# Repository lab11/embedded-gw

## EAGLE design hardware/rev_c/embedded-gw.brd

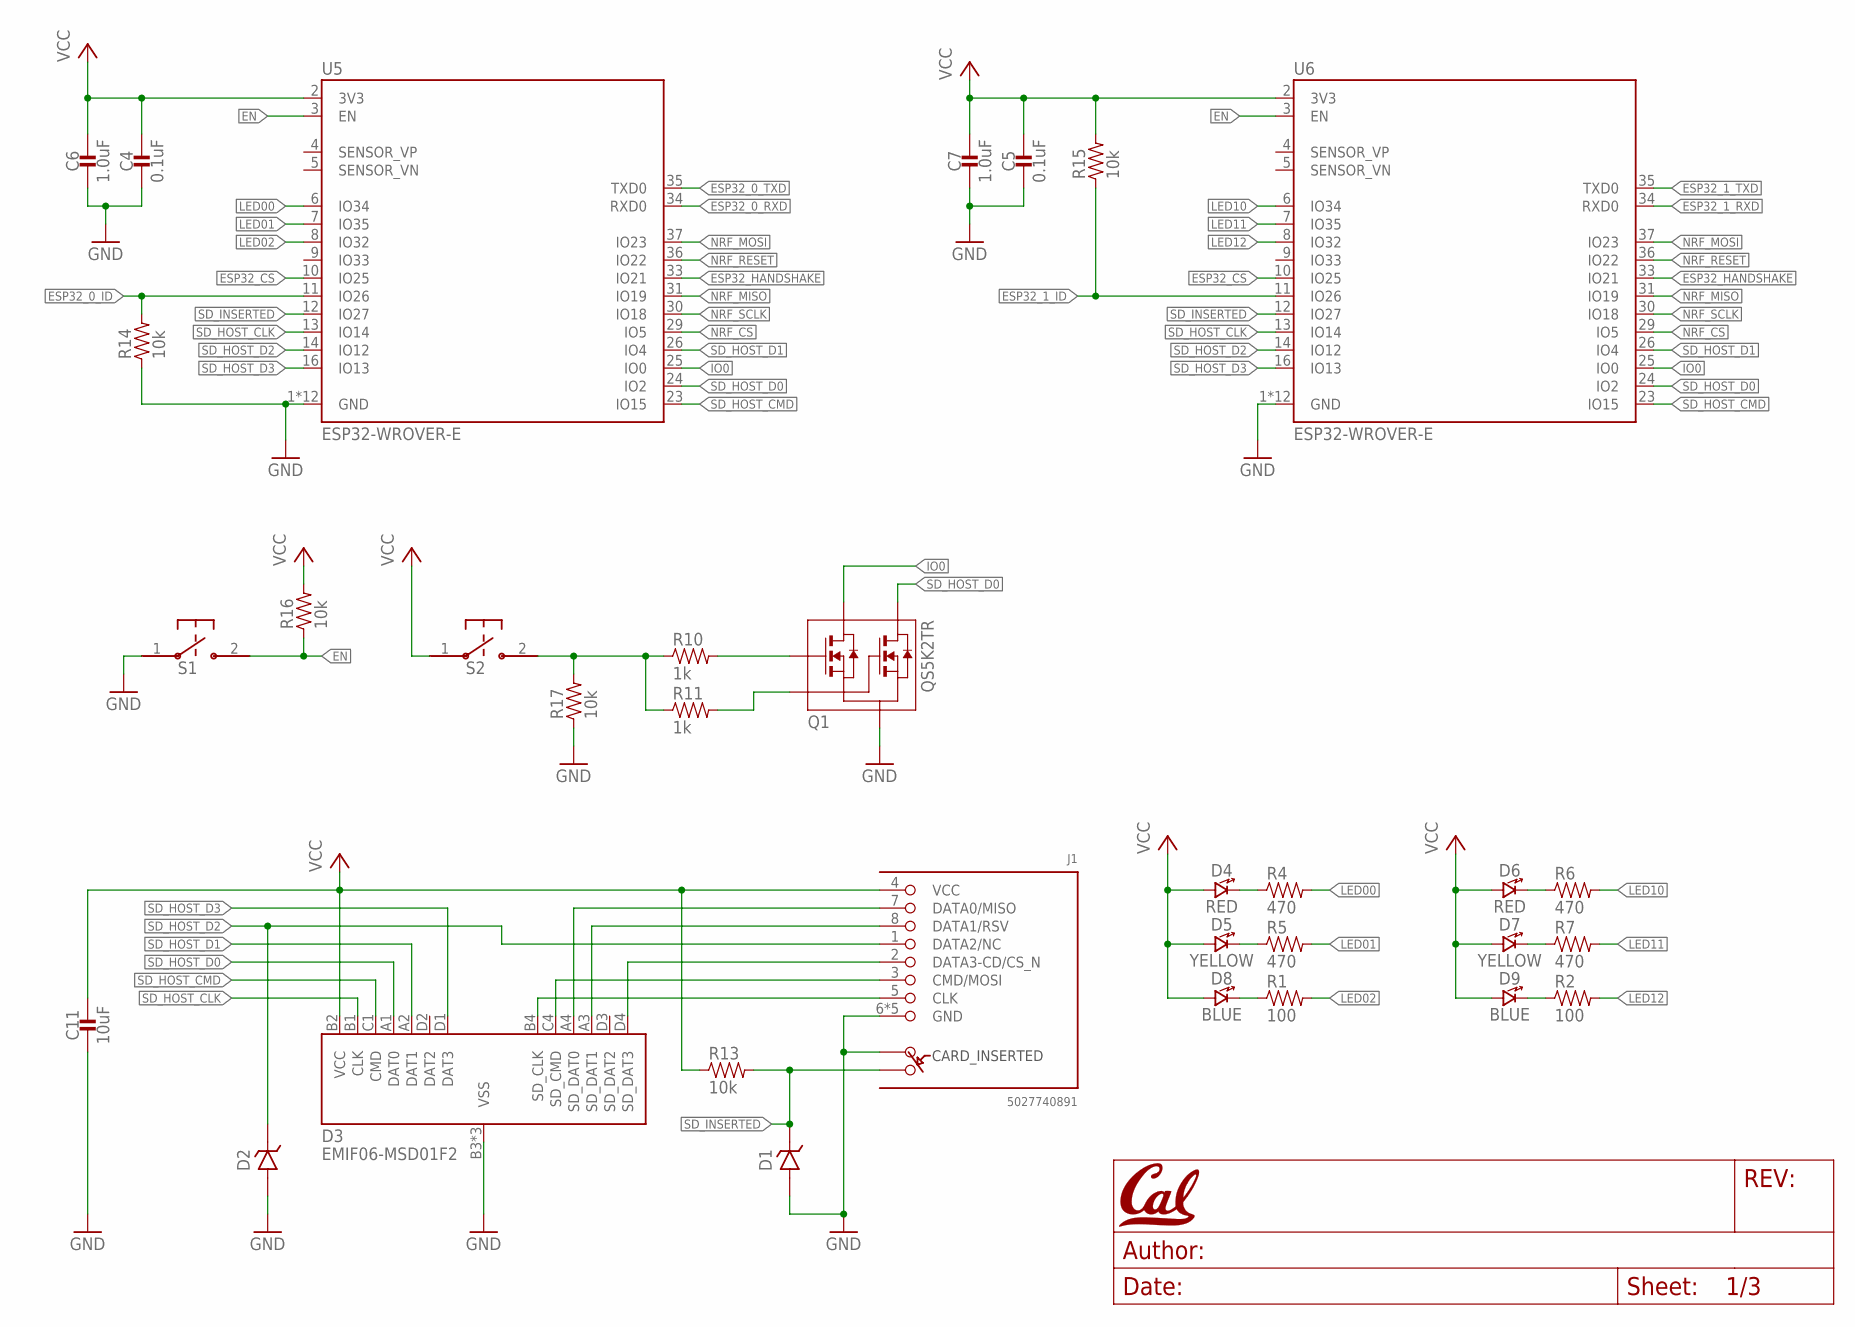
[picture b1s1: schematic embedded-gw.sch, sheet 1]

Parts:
C4, C5: 0.1uF; 0402_CAP; MPN CL05B104KQ5NNNC; DIGIKEY 1276-1511-1-ND
C6, C7: 1.0uF; 0402_CAP; MPN CL05A105KQ5NNNC; DIGIKEY 1276-1010-1-ND
C11: 10uF; 0805_CAP; MPN CL21A106KQCLNNC; DIGIKEY 1276-2404-1-ND
D1, D2: DIODE_ZENER0201; 0201_DIODE; MPN ESD7381MUT5G; DIGIKEY ESD7381MUT5GOSCT-ND
D3: EMIF06-MSD01F2; BGA16C50P4X4_192X192X65N
D4, D6: RED; LED-0603; MPN LTST-C193KRKT-5A; DIGIKEY 160-1830-1-ND
D5, D7: YELLOW; LED-0603; MPN LTST-C193KSKT-5A; DIGIKEY 160-1831-1-ND
D8, D9: BLUE; LED-0603; MPN LTST-C193TBKT-5A; DIGIKEY 160-1827-1-ND
J1: 5027740891
Q1: QS5K2TR; SOT95P280X100-5N
R1, R2: 100; 0402_RES; MPN RC0402JR-07100RL; DIGIKEY 311-100JRCT-ND
R4, R5, R6, R7: 470; 0402_RES; MPN RC0402FR-07470RL; DIGIKEY 311-470LRCT-ND
R10, R11: 1k; 0402_RES; MPN RMCF0402JT1K00; DIGIKEY RMCF0402JT1K00CT-ND
R13, R14, R15, R16, R17: 10k; 0402_RES; MPN RMCF0402JT10K0; DIGIKEY RMCF0402JT10K0CT-ND
S1, S2: B3U-1000P
U5, U6: ESP32-WROVER-E

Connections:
!NRF_RESET: U5.36 (IO22), U6.36 (IO22); also elsewhere on the board
!SD_INSERTED: D1.P$1 (CATHODE), J1.SWITCH (B), R13.2, U5.12 (IO27), U6.12 (IO27)
EN: R16.1, S1.2, U5.3 (EN), U6.3 (EN)
ESP32_0_ID: R14.2, U5.11 (IO26)
ESP32_0_RXD: U5.34 (RXD0); also elsewhere on the board
ESP32_0_TXD: U5.35 (TXD0); also elsewhere on the board
ESP32_1_ID: R15.1, U6.11 (IO26)
ESP32_1_RXD: U6.34 (RXD0); also elsewhere on the board
ESP32_1_TXD: U6.35 (TXD0); also elsewhere on the board
ESP32_CS: U5.10 (IO25), U6.10 (IO25)
ESP32_HANDSHAKE: U5.33 (IO21), U6.33 (IO21)
GND: C4.2, C5.2, C6.2, C7.2, C11.P$2 (2), D1.P$2 (ANODE), D2.P$2 (ANODE), D3.B3 (VSS), D3.C2 (VSS), D3.C3 (VSS), J1.6 (GND), J1.DETECT (A), J1.GND1 (GND), J1.GND2 (GND), J1.GND3 (GND), J1.GND4 (GND), Q1.2 (S), R14.1, R17.1, S1.1, U5.1 (GND), U5.15 (GND), U5.38 (GND), U5.GND1 (GND), U5.GND2 (GND), U5.GND3 (GND), U5.GND4 (GND), U5.GND5 (GND), U5.GND6 (GND), U5.GND7 (GND), U5.GND8 (GND), U5.GND9 (GND), U6.1 (GND), U6.15 (GND), U6.38 (GND), U6.GND1 (GND), U6.GND2 (GND), U6.GND3 (GND), U6.GND4 (GND), U6.GND5 (GND), U6.GND6 (GND), U6.GND7 (GND), U6.GND8 (GND), U6.GND9 (GND); also elsewhere on the board
IO0: Q1.5 (D1), U5.25 (IO0), U6.25 (IO0)
LED00: R4.2, U5.6 (IO34)
LED01: R5.2, U5.7 (IO35)
LED02: R1.2, U5.8 (IO32)
LED10: R6.2, U6.6 (IO34)
LED11: R7.2, U6.7 (IO35)
LED12: R2.2, U6.8 (IO32)
unnamed: Q1.1 (G1), R10.2
unnamed: Q1.3 (G2), R11.2
unnamed: R10.1, R11.1, R17.2, S2.2
unnamed: D3.C4 (SD_CMD), J1.3 (CMD/MOSI)
unnamed: D3.A4 (SD_DAT0), J1.7 (DATA0/MISO)
unnamed: D3.A3 (SD_DAT1), J1.8 (DATA1/RSV)
unnamed: D3.D4 (SD_DAT3), J1.2 (DATA3-CD/CS_N)
unnamed: D4.C (CATHODE), R4.1
unnamed: D3.B4 (SD_CLK), J1.5 (CLK)
unnamed: D5.C (CATHODE), R5.1
unnamed: D8.C (CATHODE), R1.1
unnamed: D6.C (CATHODE), R6.1
unnamed: D7.C (CATHODE), R7.1
unnamed: D9.C (CATHODE), R2.1
NRF_CS: U5.29 (IO5), U6.29 (IO5); also elsewhere on the board
NRF_MISO: U5.31 (IO19), U6.31 (IO19); also elsewhere on the board
NRF_MOSI: U5.37 (IO23), U6.37 (IO23); also elsewhere on the board
NRF_SCLK: U5.30 (IO18), U6.30 (IO18); also elsewhere on the board
SD_HOST_CLK: D3.B1 (CLK), U5.13 (IO14), U6.13 (IO14)
SD_HOST_CMD: D3.C1 (CMD), U5.23 (IO15), U6.23 (IO15)
SD_HOST_D0: D3.A1 (DAT0), Q1.4 (D2), U5.24 (IO2), U6.24 (IO2)
SD_HOST_D1: D3.A2 (DAT1), U5.26 (IO4), U6.26 (IO4)
SD_HOST_D2: D2.P$1 (CATHODE), J1.1 (DATA2/NC), U5.14 (IO12), U6.14 (IO12)
SD_HOST_D3: D3.D1 (DAT3), U5.16 (IO13), U6.16 (IO13)
VCC: C4.1, C5.1, C6.1, C7.1, C11.P$1 (1), D3.B2 (VCC), D4.A (ANODE), D5.A (ANODE), D6.A (ANODE), D7.A (ANODE), D8.A (ANODE), D9.A (ANODE), J1.4 (VCC), R13.1, R15.2, R16.2, S2.1, U5.2 (3V3), U6.2 (3V3); also elsewhere on the board

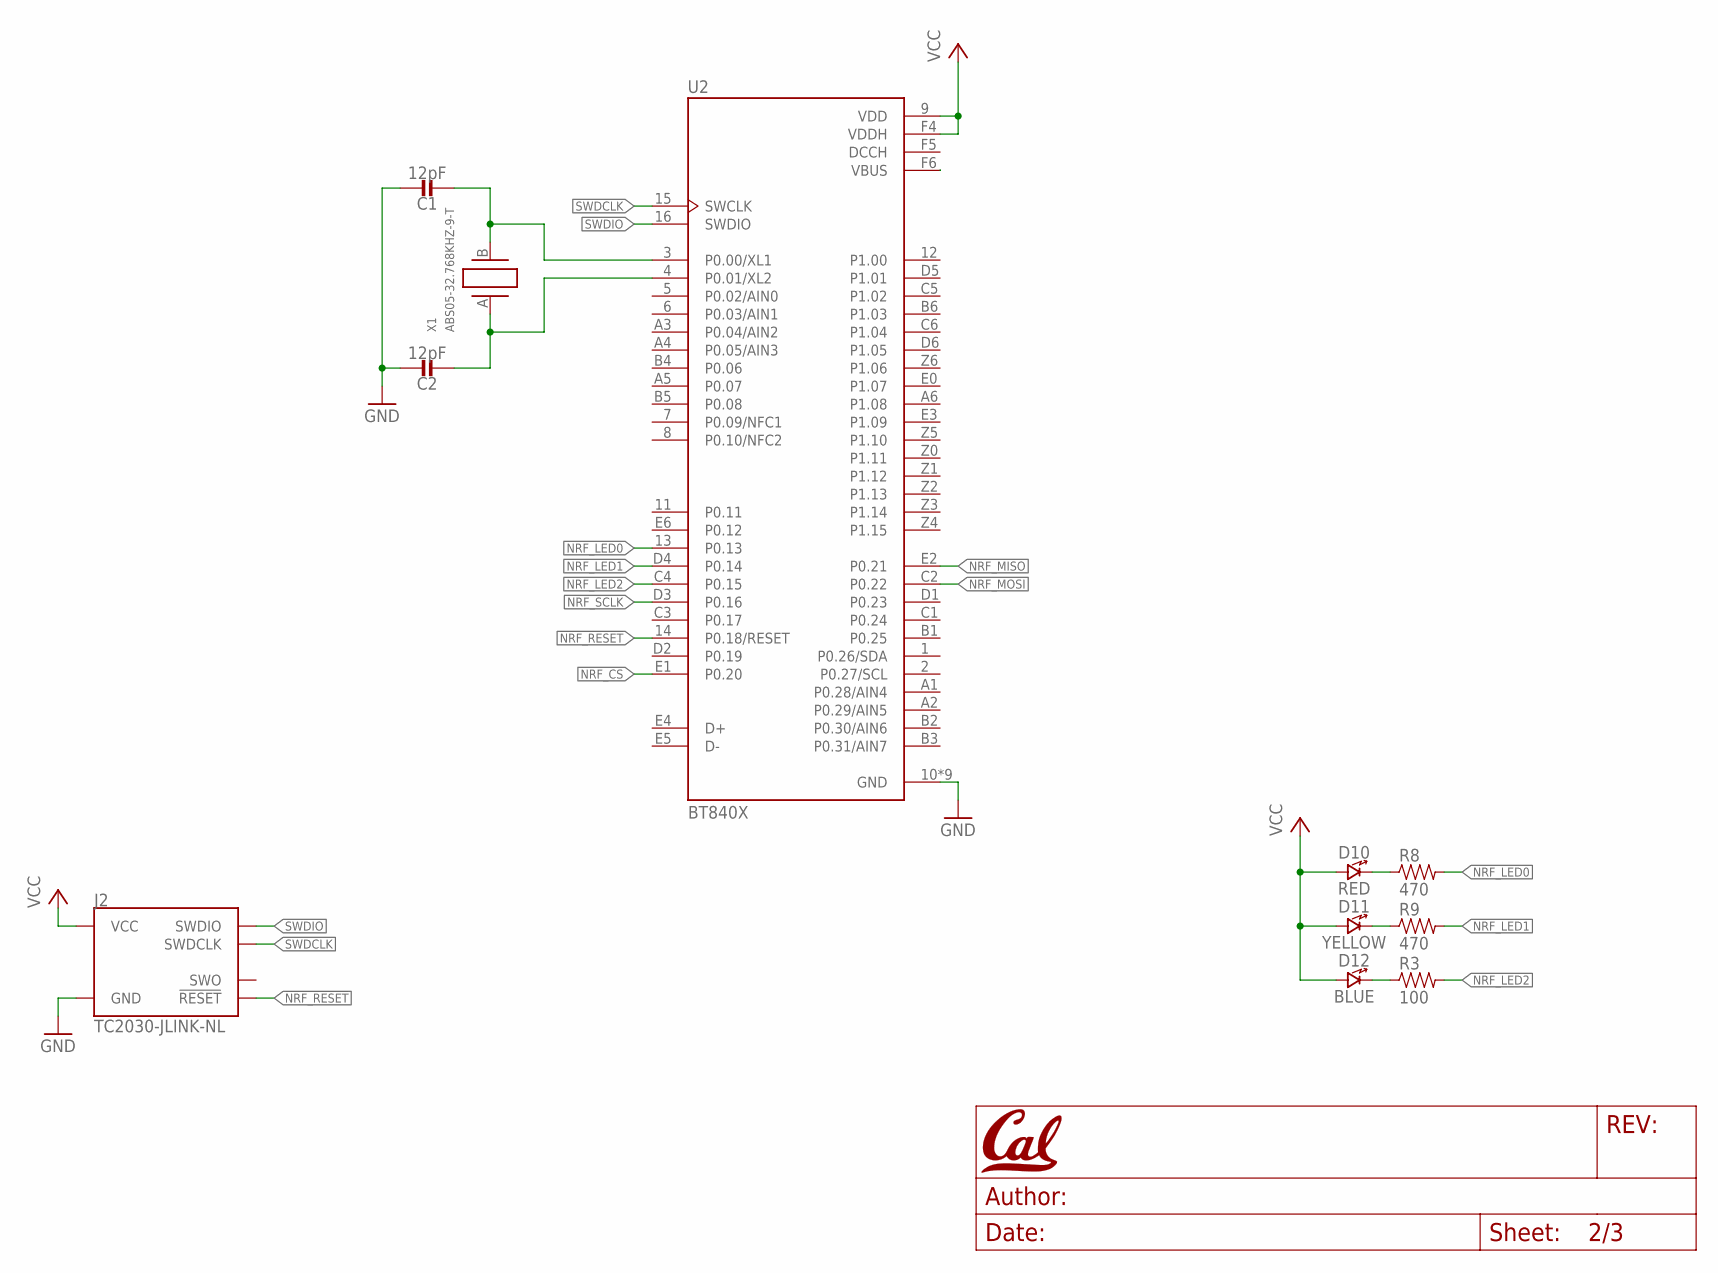
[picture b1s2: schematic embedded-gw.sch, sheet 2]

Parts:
C1, C2: 12pF; 0402_CAP; MPN GCM1555C1H120GA16D; DIGIKEY 490-GCM1555C1H120GA16DCT-ND
D10: RED; LED-0603; MPN LTST-C193KRKT-5A; DIGIKEY 160-1830-1-ND
D11: YELLOW; LED-0603; MPN LTST-C193KSKT-5A; DIGIKEY 160-1831-1-ND
D12: BLUE; LED-0603; MPN LTST-C193TBKT-5A; DIGIKEY 160-1827-1-ND
J2: TC2030-JLINK-NL; TC2030-IDC-NL
R3: 100; 0402_RES; MPN RC0402JR-07100RL; DIGIKEY 311-100JRCT-ND
R8, R9: 470; 0402_RES; MPN RC0402FR-07470RL; DIGIKEY 311-470LRCT-ND
U2: BT840X; XCVR_BT840X
X1: ABS05-32.768KHZ-9-T; ABS05

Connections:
!NRF_RESET: J2.3 (!RESET), U2.14 (P0.18/RESET); also elsewhere on the board
DCCH: U2.F5 (DCCH)
GND: C1.1, C2.1, J2.5 (GND), U2.10 (GND), U2.A0 (GND), U2.B0 (GND), U2.C0 (GND), U2.D0 (GND), U2.F0 (GND), U2.F1 (GND), U2.F2 (GND), U2.F3 (GND); also elsewhere on the board
unnamed: C1.2, U2.3 (P0.00/XL1), X1.B (2)
unnamed: C2.2, U2.4 (P0.01/XL2), X1.A (1)
unnamed: D10.C (CATHODE), R8.1
unnamed: D11.C (CATHODE), R9.1
unnamed: D12.C (CATHODE), R3.1
NC: U2.F6 (VBUS)
NRF_CS: U2.E1 (P0.20); also elsewhere on the board
NRF_LED0: R8.2, U2.13 (P0.13)
NRF_LED1: R9.2, U2.D4 (P0.14)
NRF_LED2: R3.2, U2.C4 (P0.15)
NRF_MISO: U2.E2 (P0.21); also elsewhere on the board
NRF_MOSI: U2.C2 (P0.22); also elsewhere on the board
NRF_SCLK: U2.D3 (P0.16); also elsewhere on the board
SWDCLK: J2.4 (SWDCLK), U2.15 (SWCLK)
SWDIO: J2.2 (SWDIO), U2.16 (SWDIO)
VCC: D10.A (ANODE), D11.A (ANODE), D12.A (ANODE), J2.1 (VCC), U2.9 (VDD), U2.F4 (VDDH); also elsewhere on the board

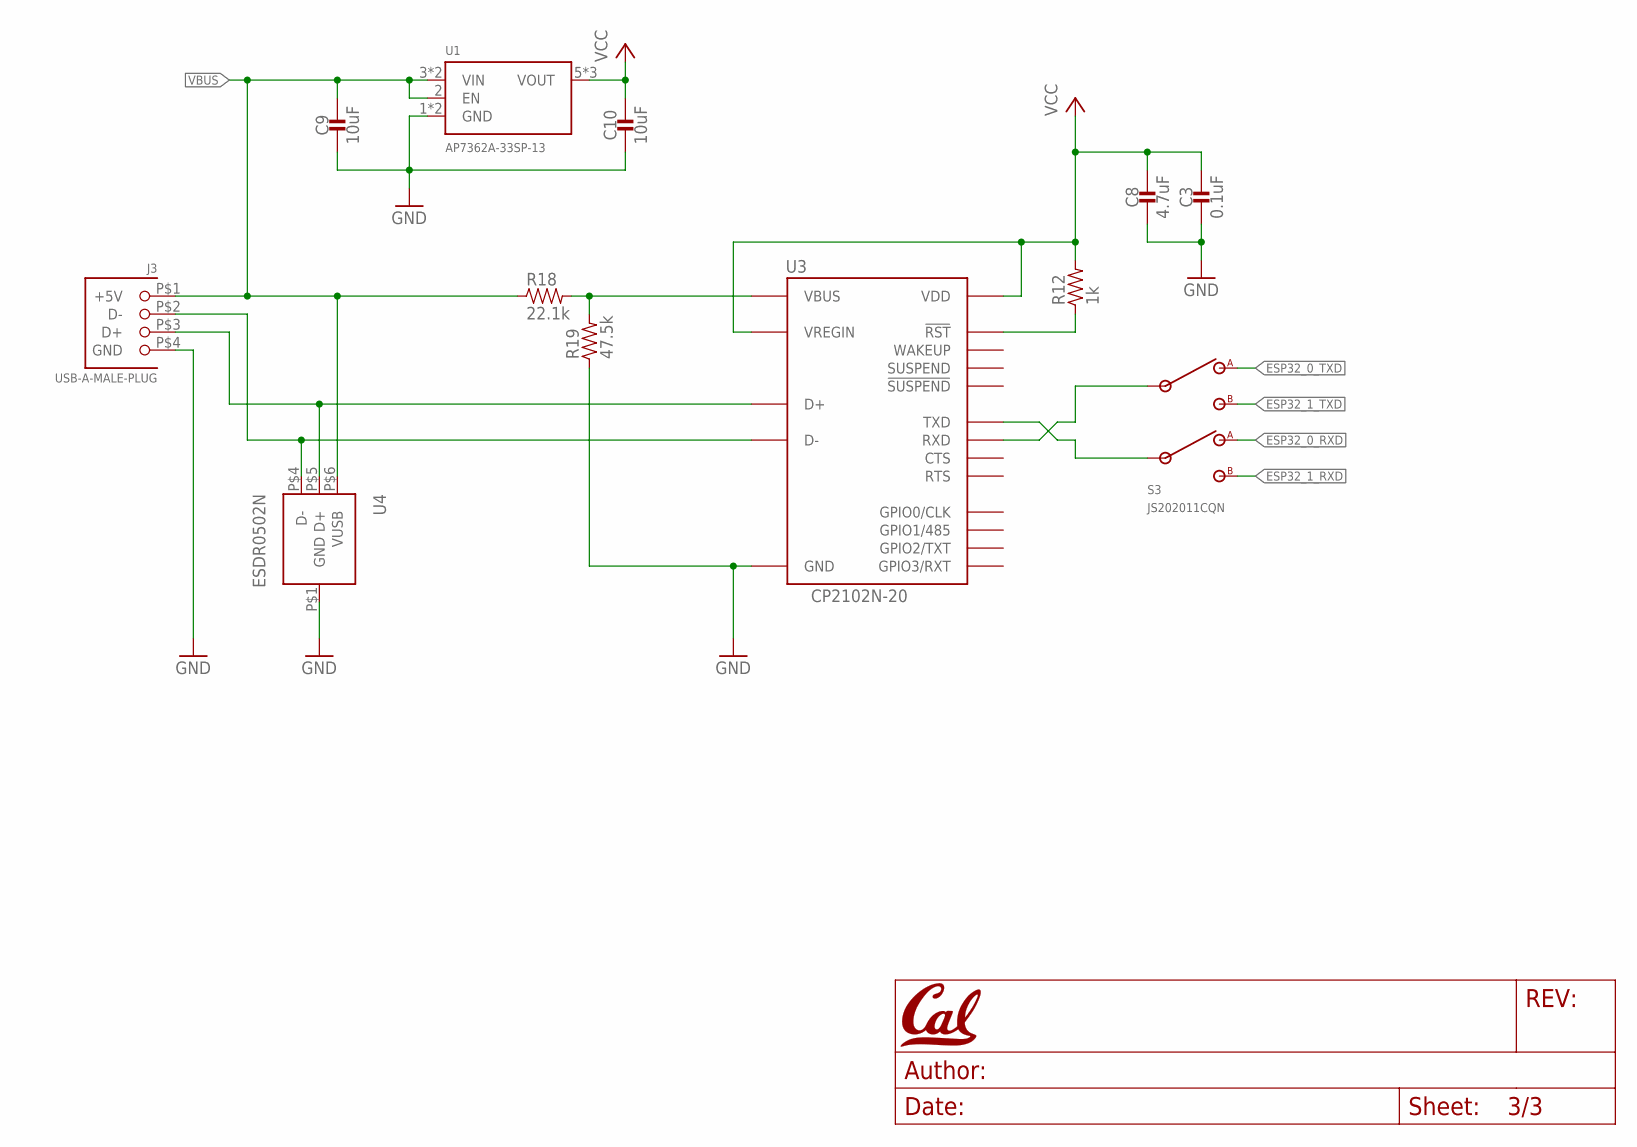
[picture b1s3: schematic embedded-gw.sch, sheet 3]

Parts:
C3: 0.1uF; 0402_CAP; MPN CL05B104KQ5NNNC; DIGIKEY 1276-1511-1-ND
C8: 4.7uF; 0603_CAP; MPN CL10A475KQ8NNNC; DIGIKEY 1276-1045-1-ND
C9, C10: 10uF; 0805_CAP; MPN CL21A106KQCLNNC; DIGIKEY 1276-2404-1-ND
J3: USB-A-MALE-PLUG; USB_A_MALE_PLUG_CUI_UP2-AH
R12: 1k; 0402_RES; MPN RMCF0402JT1K00; DIGIKEY RMCF0402JT1K00CT-ND
R18: 22.1k; 0402_RES; MPN RC0402FR-0722K1L; DIGIKEY 311-22.1KLRCT-ND
R19: 47.5k; 0402_RES; MPN RT0402FRE0747K5L; DIGIKEY 13-RT0402FRE0747K5LCT-ND
S3: JS202011CQN
U1: AP7362A-33SP-13; SO-8EP
U3: CP2102N-20; QFN-20-3MM
U4: ESDR0502N; UDFN-6

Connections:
D+: J3.P$3 (D+), U3.4 (D+), U4.P$5 (D+)
D-: J3.P$2 (D-), U3.5 (D-), U4.P$4 (D-)
ESP32_0_RXD: S3.1 (A2); also elsewhere on the board
ESP32_0_TXD: S3.4 (A1); also elsewhere on the board
ESP32_1_RXD: S3.3 (B2); also elsewhere on the board
ESP32_1_TXD: S3.6 (B1); also elsewhere on the board
GND: C3.2, C8.2, C9.P$2 (2), C10.P$2 (2), J3.P$4 (GND), R19.1, U1.1 (GND), U1.PAD (GND), U3.3 (GND), U3.12 (GND), U3.P$1 (GND), U4.P$1 (GND); also elsewhere on the board
unnamed: R12.1, U3.9 (!RST)
unnamed: R18.2, R19.2, U3.8 (VBUS)
RXD: S3.2 (I2), U3.18 (TXD)
TXD: S3.5 (I1), U3.17 (RXD)
VBUS: C9.P$1 (1), J3.P$1 (+5V), R18.1, U1.2 (EN), U1.3 (VIN), U1.4 (VIN), U4.P$6 (VUSB)
VCC: C3.1, C8.1, C10.P$1 (1), R12.2, U1.5 (VOUT), U1.6 (VOUT), U1.7 (VOUT), U3.6 (VDD), U3.7 (VREGIN); also elsewhere on the board

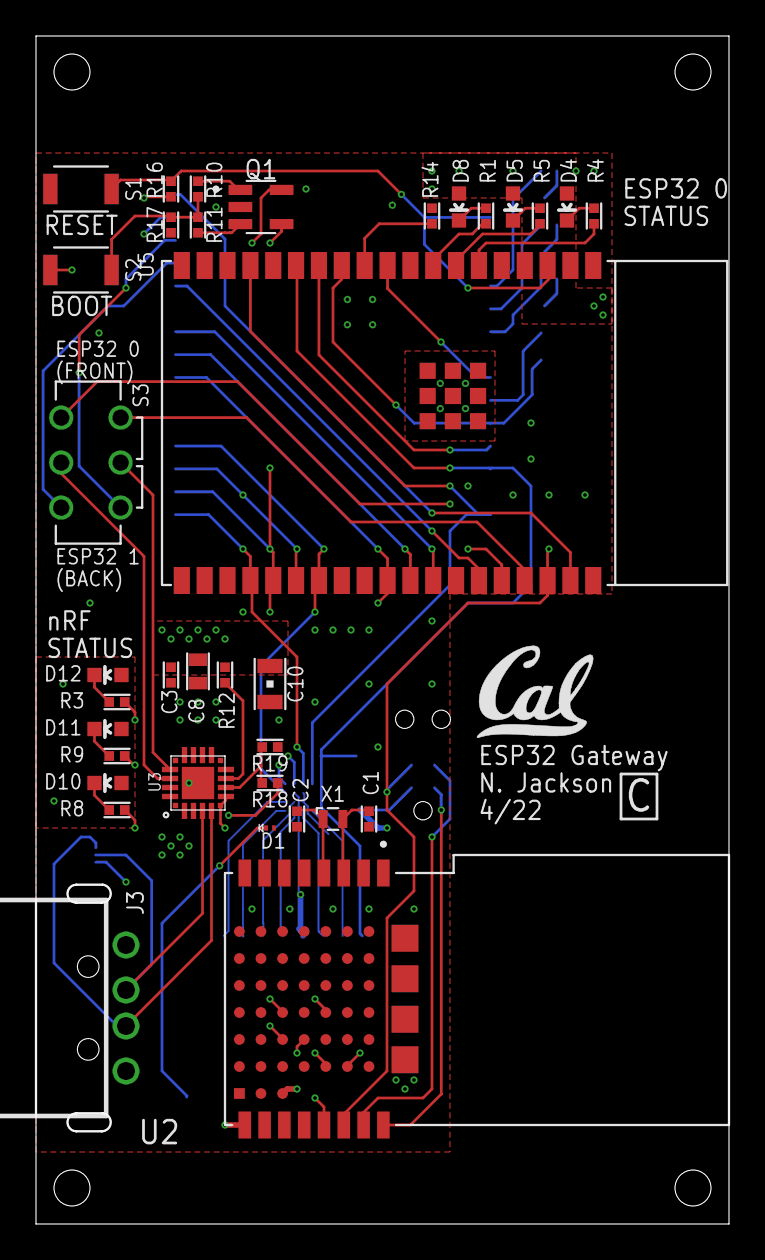
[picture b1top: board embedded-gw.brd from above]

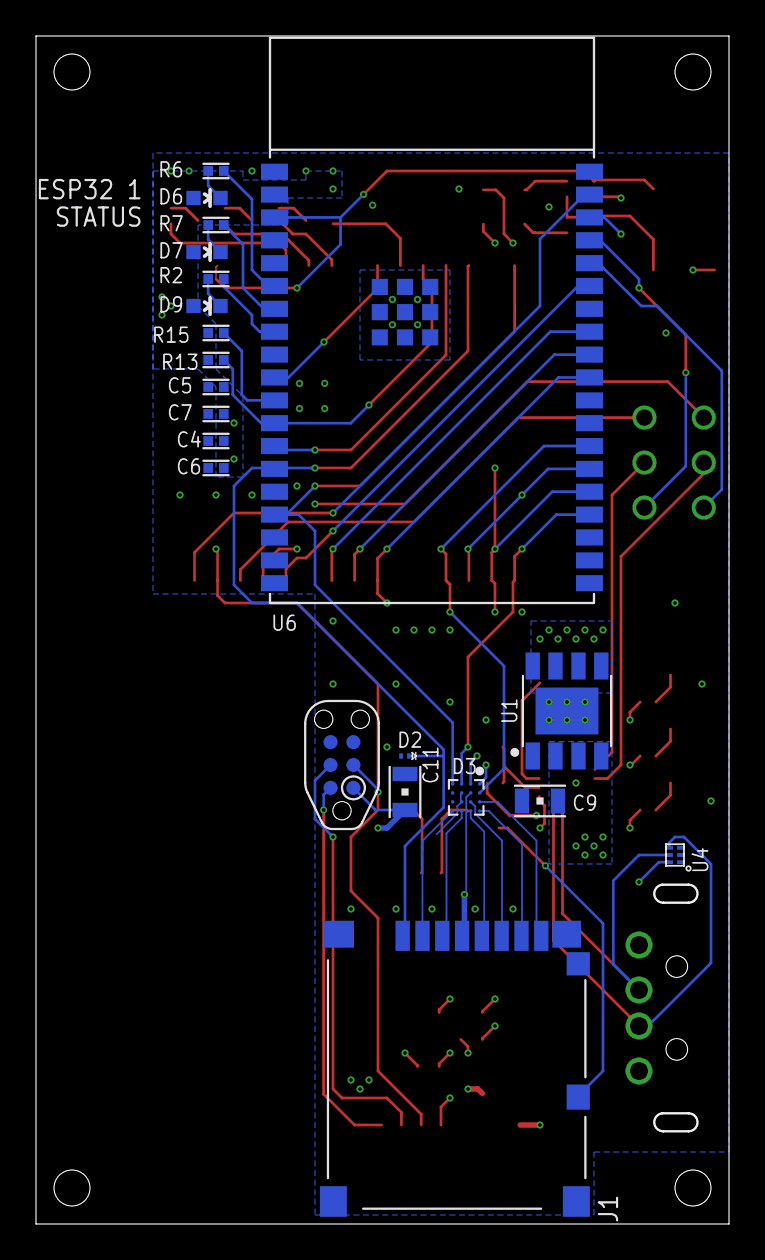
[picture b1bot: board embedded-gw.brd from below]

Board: 4 copper layers, 38.4 x 65.9 mm, 57 parts (21 on the bottom side), 61 nets.

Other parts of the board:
U$4: UCB_CAL_200MIL

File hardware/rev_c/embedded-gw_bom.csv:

# Bill of Materials,,,,,,,,,
# Converted from {},,,,,,,,,
# Generated by bom_to_text.py,,,,,,,,,
#,,,,,,,,,
,,,,,,,,,
Qty,Value,Device,Package,Parts,Description,DIGIKEY,MANUFACTURER,MOUSER,MPN
2,,DIODE_ZENER0201,0201_DIODE,"D1,D2",,ESD7381MUT5GOSCT-ND,,,ESD7381MUT5G
3,0.1uF,CAPACITOR0402_CAP,0402_CAP,"C3,C4,C5",SMD Capacitor,1276-1511-1-ND,,,CL05B104KQ5NNNC
2,1.0uF,CAPACITOR0402_CAP,0402_CAP,"C6,C7",SMD Capacitor,1276-1010-1-ND,,,CL05A105KQ5NNNC
3,100,RESISTOR0402_RES,0402_RES,"R1,R2,R3",Resistor,311-100JRCT-ND,,,RC0402JR-07100RL
5,10k,RESISTOR0402_RES,0402_RES,"R13,R14,R15,R16,R17",Resistor,RMCF0402JT10K0CT-ND,,,RMCF0402JT10K0
3,10uF,CAPACITOR0805_CAP,0805_CAP,"C9,C10,C11",SMD Capacitor,1276-2404-1-ND,,,CL21A106KQCLNNC
2,12pF,CAPACITOR0402_CAP,0402_CAP,"C1,C2",SMD Capacitor,490-GCM1555C1H120GA16DCT-ND,,,GCM1555C1H120GA16D
3,1k,RESISTOR0402_RES,0402_RES,"R10,R11,R12",Resistor,RMCF0402JT1K00CT-ND,,,RMCF0402JT1K00
1,22.1k,RESISTOR0402_RES,0402_RES,R18,Resistor,311-22.1KLRCT-ND,,,RC0402FR-0722K1L
1,4.7uF,CAPACITOR0603_CAP,0603_CAP,C8,SMD Capacitor,1276-1045-1-ND,,,CL10A475KQ8NNNC
1,47.5k,RESISTOR0402_RES,0402_RES,R19,Resistor,13-RT0402FRE0747K5LCT-ND,,,RT0402FRE0747K5L
6,470,RESISTOR0402_RES,0402_RES,"R4,R5,R6,R7,R8,R9",Resistor,311-470LRCT-ND,,,RC0402FR-07470RL
1,5027740891,5027740891,5027740891,J1,CONN MICRO SD CARD PUSH-PUSH R/A,WM24066CT-ND,Molex,,5027740891
1,ABS05-32.768KHZ-9-T,ABS05-32.768KHZ-9-T,ABS05,X1,32.768kHz Crystal,535-11897-1-ND,Abracon,,ABS05-32.768KHZ-9-T
1,AP7362A-33SP-13,AP7362A-33SP-13,SO-8EP,U1,The AP7362 is a 1.5A adjustable/fixed output voltage linear regulator with,AP7362A-33SP-13DICT-ND,Diodes Incorporated,,AP7362A-33SP-13 
2,B3U-1000P,B3U-1000P,B3U-1000P,"S1,S2",Switch,SW1020CT-ND,Omron,,B3U-1000P
3,BLUE,LED0603,LED-0603,"D8,D9,D12",LED,160-1827-1-ND,,,LTST-C193TBKT-5A
1,BT840X,BT840X,XCVR_BT840X,U2,"802.15.4, Bluetooth Bluetooth v5.0, Thread, Zigbee® Transceiver Module 2.4GHz PCB Trace Surface Mou  Check prices",1914-BT840XCT-ND,Fanstel Corp.,,BT840X
1,CP2102N-20,CP2102N-20,QFN-20-3MM,U3,"A cheap, simple USB to UART adapter",336-5885-ND,SiLabs,,CP2102N-A02-GQFN20
1,EMIF06-MSD01F2,EMIF06-MSD01F2,BGA16C50P4X4_192X192X65N,D3,Mini and micro SD Card - EMI filtering and 25 kV ESD protection,497-5903-1-ND,STMicroelectronics,511-EMIF06-MSD01F2,EMIF06-MSD01F2
1,ESDR0502N,ESDR0502N,UDFN-6,U4,,ESDR0502NMUTBGOSCT-ND,,,ESDR0502NMUTBG
2,ESP32-WROVER-E,ESP32-WROVER-E,ESP32-WROVER-E,"U5,U6",,1965-ESP32-WROVER-E(8MB)CT-ND,Espressif Systems,,  ESP32-WROVER-E (8MB)
1,JS202011CQN,JS202011CQN,JS202011CQN,S3,DPDT through hole,401-2001-ND,C&K,,JS202011CQN
1,QS5K2TR,QS5K2TR,SOT95P280X100-5N,Q1,2.5V Drive Nch+Nch MOSFET,QS5K2CT-ND,Rohm,,QS5K2TR
3,RED,LED0603,LED-0603,"D4,D6,D10",LED,160-1830-1-ND,,,LTST-C193KRKT-5A
1,USB-A-MALE-PLUG,USB-A-MALE-PLUG,USB_A_MALE_PLUG_CUI_UP2-AH,J3,USB A Male plug connector,102-3996-ND,CUI,,UP2-AH-1-TH
3,YELLOW,LED0603,LED-0603,"D5,D7,D11",LED,160-1831-1-ND,,,LTST-C193KSKT-5A

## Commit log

2021-03-31 schematic done-ish
2021-03-31 forgot to save
2021-04-13 start layout
2021-04-13 nothing to do
2021-04-14 fix labels
2021-04-15 Clean up and run the script
    rename parts, clean up bom, cam, package up
2021-04-20 leave gpio12 floating, add diode
2021-05-10 add pdf
2021-05-11 revb - disable bridge regulator
2021-07-20 Change handshake gpio from 33 to 21, add ipc
2021-07-20 update date to now
2021-07-28 Swap Q1 with QS5K2TR
2022-03-29 add mounting holes
2022-03-30 Add fusion360 enclosure design
2022-04-22 replace sd card slot
2022-04-27 change sclk to pin 16 instead of PA 19
2022-05-11 update BOM
2022-05-16 add sd card slot + stl files
2022-06-08 update screw socket in case top
